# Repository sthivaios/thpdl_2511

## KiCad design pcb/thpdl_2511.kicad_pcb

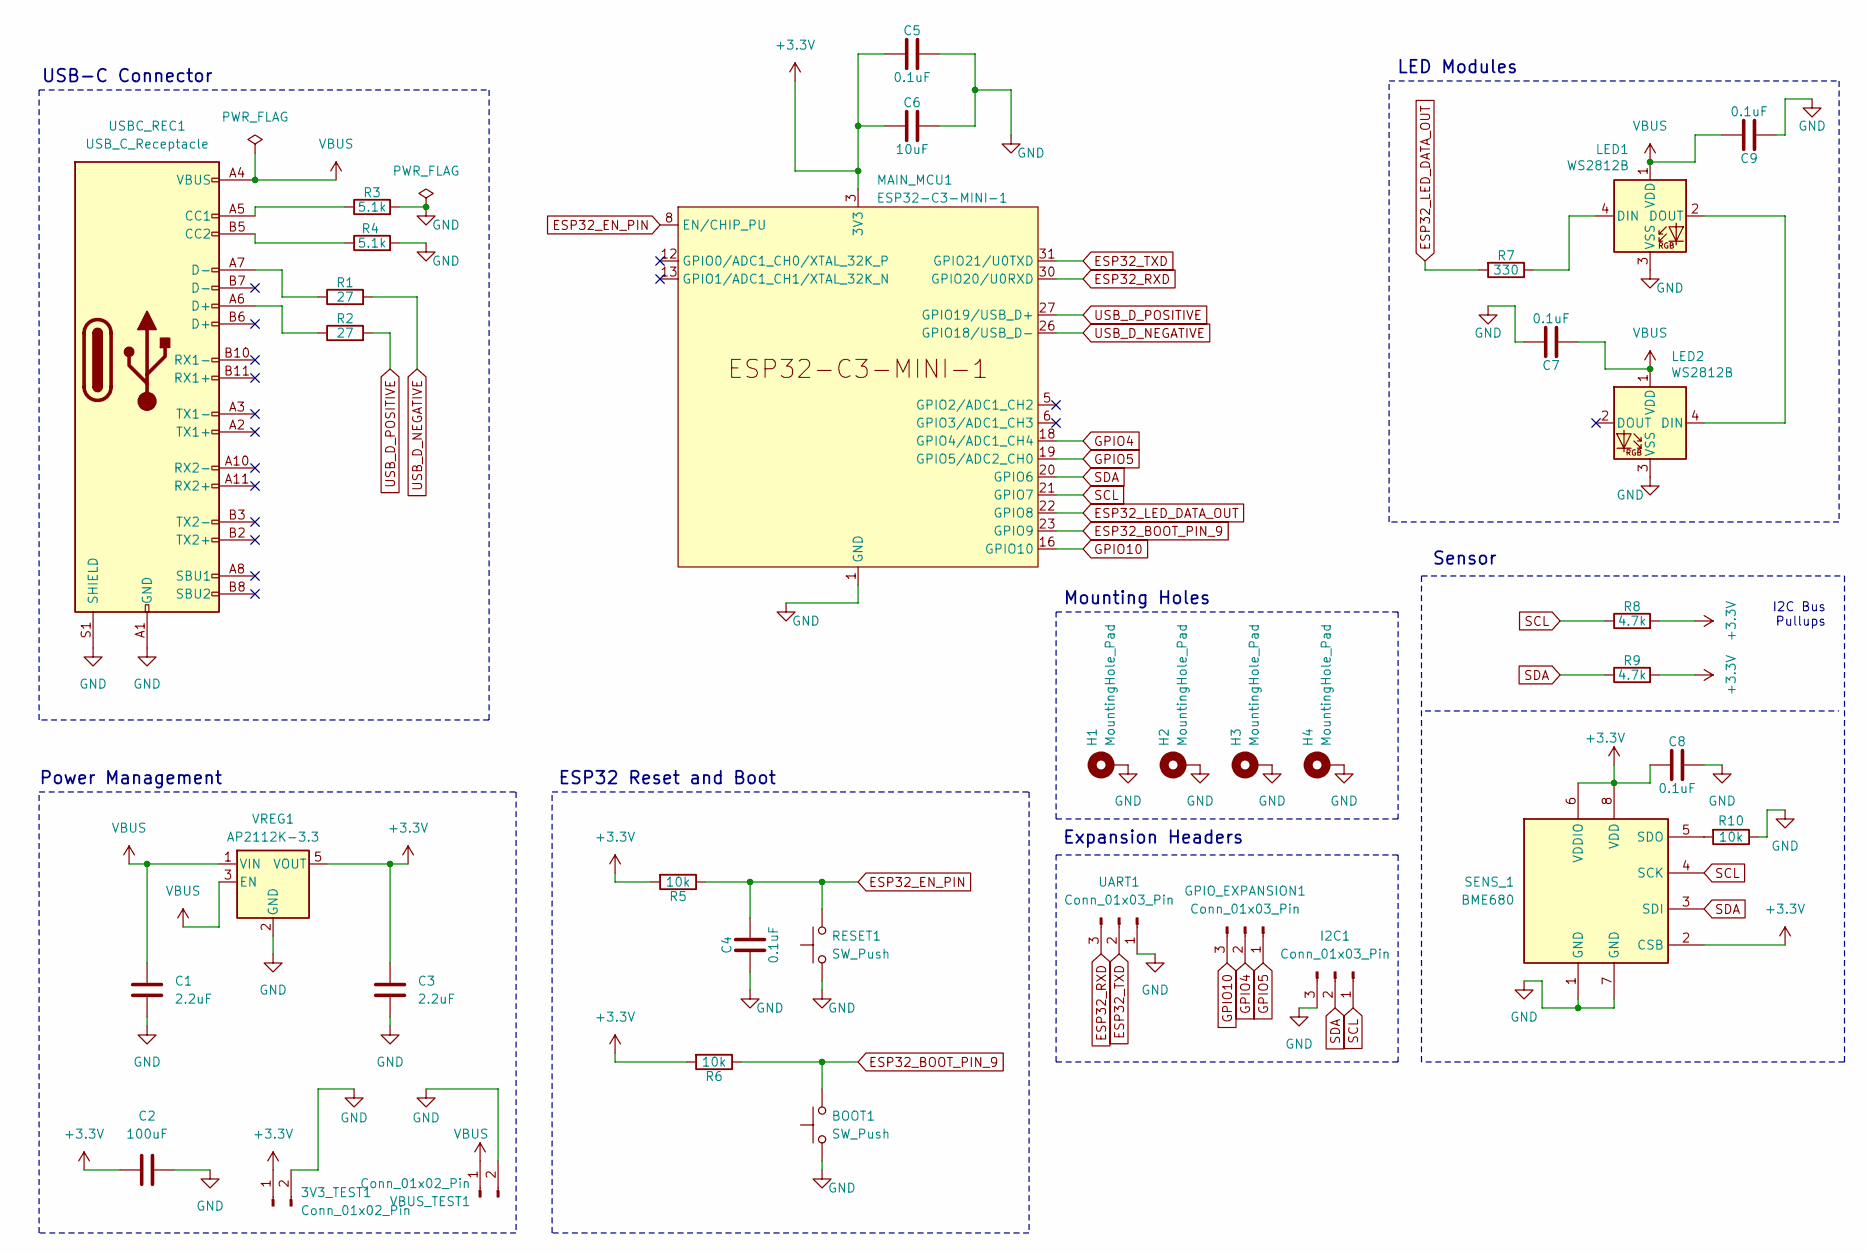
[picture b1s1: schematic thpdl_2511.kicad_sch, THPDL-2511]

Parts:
3V3_TEST1: Conn_01x02_Pin; PinHeader_1x02_P2.54mm_Vertical; LCSC C492401
BOOT1: SW_Push; SW_Push_1P1T_NO_CK_KSC7xxJ; LCSC C221766
C1, C3: 2.2uF; C_0201_0603Metric; LCSC C76933
C2: 100uF; C_0805_2012Metric; LCSC C15850
C4, C5, C7, C8, C9: 0.1uF; C_0201_0603Metric; LCSC C1525
C6: 10uF; C_0201_0603Metric; LCSC C19702
GPIO_EXPANSION1: Conn_01x03_Pin; PinHeader_1x03_P2.54mm_Vertical; LCSC C2937625
H1, H2, H3, H4: MountingHole_Pad; MountingHole_3.2mm_M3_Pad_TopBottom
I2C1: Conn_01x03_Pin; PinHeader_1x03_P2.54mm_Vertical; LCSC C2937625
LED1, LED2: WS2812B; LED_WS2812B_PLCC4_5.0x5.0mm_P3.2mm; LCSC C2843785
MAIN_MCU1: ESP32-C3-MINI-1; LCSC C2838502
R1, R2: 27; C_0201_0603Metric; LCSC C270320
R3, R4: 5.1k; C_0201_0603Metric; LCSC C473471
R5, R6, R10: 10k; C_0201_0603Metric; LCSC C473048
R7: 330; C_0201_0603Metric; LCSC C274872
R8, R9: 4.7k; C_0201_0603Metric; LCSC C270346
RESET1: SW_Push; SW_Push_1P1T_NO_CK_KSC7xxJ; LCSC C221766
SENS_1: BME680; Bosch_LGA-8_3x3mm_P0.8mm_ClockwisePinNumbering; LCSC C125972
UART1: Conn_01x03_Pin; PinHeader_1x03_P2.54mm_Vertical; LCSC C2937625
USBC_REC1: USB_C_Receptacle; USB_C_Receptacle_G-Switch_GT-USB-7010ASV; LCSC C2988369
VBUS_TEST1: Conn_01x02_Pin; PinHeader_1x02_P2.54mm_Vertical; LCSC C492401
VREG1: AP2112K-3.3; SOT-23-5; LCSC C51118

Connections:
+3.3V: 3V3_TEST1.1, C2.1, C3.1, C5.2, C6.2, C8.2, MAIN_MCU1.3 (3V3), R5.2, R6.2, R8.2, R9.2, SENS_1.2 (CSB), SENS_1.6 (VDDIO), SENS_1.8 (VDD), VREG1.5 (VOUT)
ESP32_BOOT_PIN_9: BOOT1.2, MAIN_MCU1.23 (GPIO9), R6.1
ESP32_EN_PIN: C4.1, MAIN_MCU1.8 (EN/CHIP_PU), R5.1, RESET1.2
ESP32_LED_DATA_OUT: MAIN_MCU1.22 (GPIO8), R7.2
ESP32_RXD: MAIN_MCU1.30 (GPIO20/U0RXD), UART1.3
ESP32_TXD: MAIN_MCU1.31 (GPIO21/U0TXD), UART1.2
GND: 3V3_TEST1.2, BOOT1.1, C1.2, C2.2, C3.2, C4.2, C5.1, C6.1, C7.2, C8.1, C9.2, H1.1, H2.1, H3.1, H4.1, I2C1.3, LED1.3 (VSS), LED2.3 (VSS), MAIN_MCU1.1 (GND), MAIN_MCU1.2 (GND), MAIN_MCU1.11 (GND), MAIN_MCU1.14 (GND), MAIN_MCU1.36 (GND), MAIN_MCU1.37 (GND), MAIN_MCU1.38 (GND), MAIN_MCU1.39 (GND), MAIN_MCU1.40 (GND), MAIN_MCU1.41 (GND), MAIN_MCU1.42 (GND), MAIN_MCU1.43 (GND), MAIN_MCU1.44 (GND), MAIN_MCU1.45 (GND), MAIN_MCU1.46 (GND), MAIN_MCU1.47 (GND), MAIN_MCU1.48 (GND), MAIN_MCU1.49 (GND), MAIN_MCU1.50 (GND), MAIN_MCU1.51 (GND), MAIN_MCU1.52 (GND), MAIN_MCU1.53 (GND), R3.2, R4.2, R10.1, RESET1.1, SENS_1.1 (GND), SENS_1.7 (GND), UART1.1, USBC_REC1.A1 (GND), USBC_REC1.A12 (GND), USBC_REC1.B1 (GND), USBC_REC1.B12 (GND), USBC_REC1.S1 (SHIELD), VBUS_TEST1.2, VREG1.2 (GND)
GPIO4: GPIO_EXPANSION1.2, MAIN_MCU1.18 (GPIO4/ADC1_CH4)
GPIO5: GPIO_EXPANSION1.1, MAIN_MCU1.19 (GPIO5/ADC2_CH0)
GPIO10: GPIO_EXPANSION1.3, MAIN_MCU1.16 (GPIO10)
unnamed: LED1.4 (DIN), R7.1
unnamed: LED1.2 (DOUT), LED2.4 (DIN)
unnamed: R1.1, USBC_REC1.A7 (D-)
unnamed: R2.1, USBC_REC1.A6 (D+)
unnamed: R10.2, SENS_1.5 (SDO)
unnamed: R3.1, USBC_REC1.A5 (CC1)
unnamed: R4.1, USBC_REC1.B5 (CC2)
SCL: I2C1.1, MAIN_MCU1.21 (GPIO7), R8.1, SENS_1.4 (SCK)
SDA: I2C1.2, MAIN_MCU1.20 (GPIO6), R9.1, SENS_1.3 (SDI)
USB_D_NEGATIVE: MAIN_MCU1.26 (GPIO18/USB_D-), R1.2
USB_D_POSITIVE: MAIN_MCU1.27 (GPIO19/USB_D+), R2.2
VBUS: C1.1, C7.1, C9.1, LED1.1 (VDD), LED2.1 (VDD), USBC_REC1.A4 (VBUS), USBC_REC1.A9 (VBUS), USBC_REC1.B4 (VBUS), USBC_REC1.B9 (VBUS), VBUS_TEST1.1, VREG1.1 (VIN), VREG1.3 (EN)

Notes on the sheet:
Mounting Holes
ESP32 Reset and Boot
Power Management
USB-C Connector
Expansion Headers
LED Modules
Sensor
I2C Bus Pullups

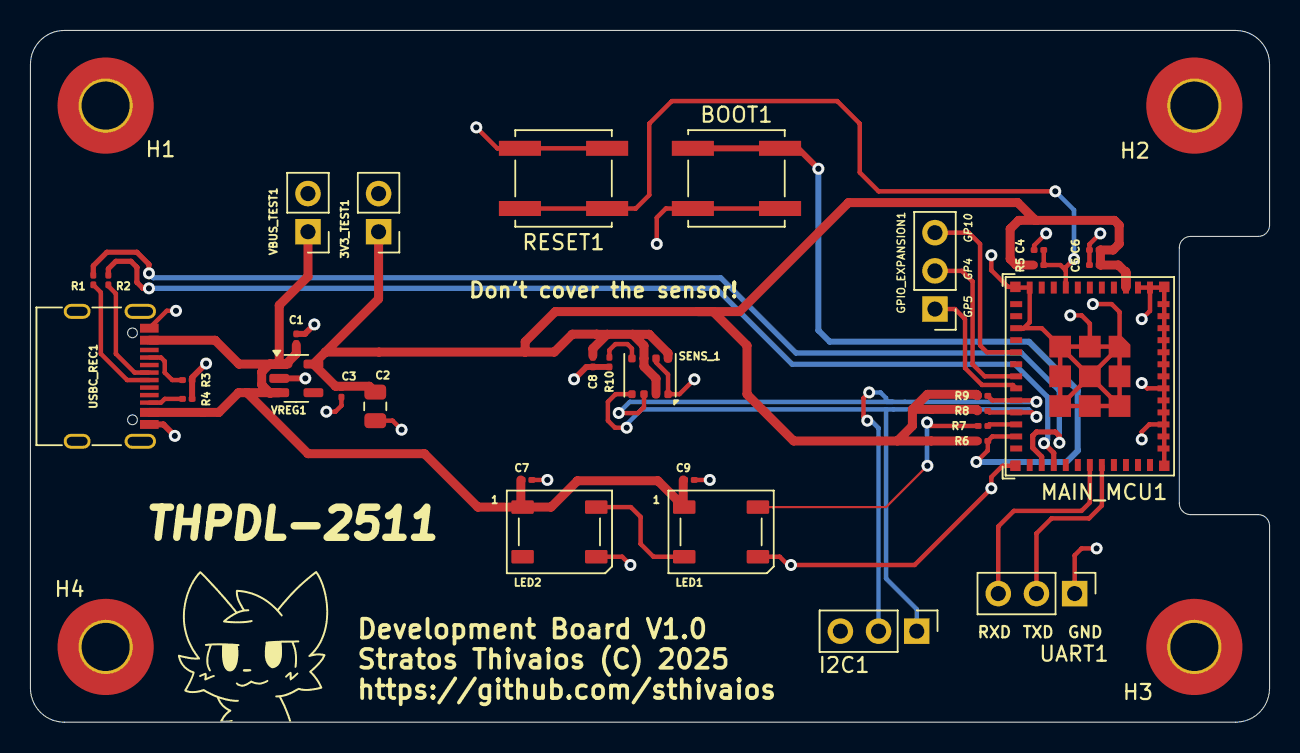
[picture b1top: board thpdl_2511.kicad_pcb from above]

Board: 2 copper layers, 82.4 x 46.0 mm, 36 parts (0 on the bottom side), 22 nets.

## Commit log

2025-11-30 init
2025-11-30 add pcb version to silkscreen and add 3d redner pic to readme
2025-11-30 i cant use markdown
2025-11-30 fixed silkscreen on esp32 footprint and update drawing sheet info table
2025-11-30 update drawing sheet table on schematic too
2025-11-30 add i2c header

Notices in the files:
pcb/thpdl_2511.kicad_pcb:
Stratos Thivaios (c) 2025 - https://github.com/sthivaios
